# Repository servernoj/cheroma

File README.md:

# CheRoMa -- Chess Robotic Manipulator

This project represents work files to build and program a 4-DOF robotic manipulator intended to move chess pieces on the board by following live game broadcasted from chess.com (and lichess.org in near future) platforms. The arm is built from budgetary parts (servos, electromagnet, brackets) readily available for purchase from Amazon and other retailers. It also has a number of custom made 3D printed parts with CAD designs included in this repo.

As of April'26 this is a "work in progress" with completion rate of roughly 70-80%. The biggest challenge so far is the lack of precision of budgetary servos that negatively affects positioning of the arm in 3D space (error ±10mm) , which in turn results in inability for the arm to move specific chess piece from/to target position. This problem is being addressed by introducing a Digitizer -- platform allowing to calibrate robot's model params in real time by forcing it to move to specific positions and automatically reading 3D coordinates of the arrival point and using this data to fit model coefficients. 

## Demos

- Cheroma arm moving chess pieces https://www.youtube.com/shorts/CEkricqCiFo
- Cheroma Digitizer prototype is used for arm calibration https://www.youtube.com/shorts/9hFcoPiPavI

# Install the service

## Install NVM + Node + PNPM

Follow steps from https://github.com/nvm-sh/nvm?tab=readme-ov-file#installing-and-updating to install NVM

Then install `Node 22` and `pnpm`
```sh
nvm install 22
nvm alias default 22
npm i -g npm
```

## Install GitHub actions runner

Follow steps in `https://github.com/<username>/<repo>/settings/actions/runners/new`

## Install systemd service

Create file `/etc/systemd/system/cheroma.service` with the following content

```` ini
[Unit]
Description=CheRoMa API Service
After=network.target

[Service]
Type=simple
User=<username>
WorkingDirectory=/home/<username>/cheroma/apps/api
ExecStart=/bin/bash -lc 'source $HOME/.nvm/nvm.sh && node --env-file .env src/index.js'
Restart=on-failure
RestartSec=5
Environment=NODE_ENV=production
TimeoutStopSec=30s
KillSignal=SIGTERM
SendSIGKILL=yes

[Install]
WantedBy=multi-user.target
````
**Note**: replace `<username>` with your actual username on RasPi

Initialize the unit
```` sh
sudo systemctl daemon-reload
sudo systemctl start cheroma.service
````

Use the following to monitor the logs at realtime
```` sh
journalctl -u cheroma -f
```` 

# Misc
```sh
i2cset -y 1 0x40 0x00 0x10 # sleep
i2cset -y 1 0x40 0xFE 0x79 # frequency 50Hz
i2cset -y 1 0x40 0x00 0x20 # wake up + set auto-inc
i2cset -y 1 0x40 0x01 0x0C # set output + configure PWM reload logic

i2cset -y 1 0x40 0x06 0x00 0x00 0x40 0x01 i # center
```

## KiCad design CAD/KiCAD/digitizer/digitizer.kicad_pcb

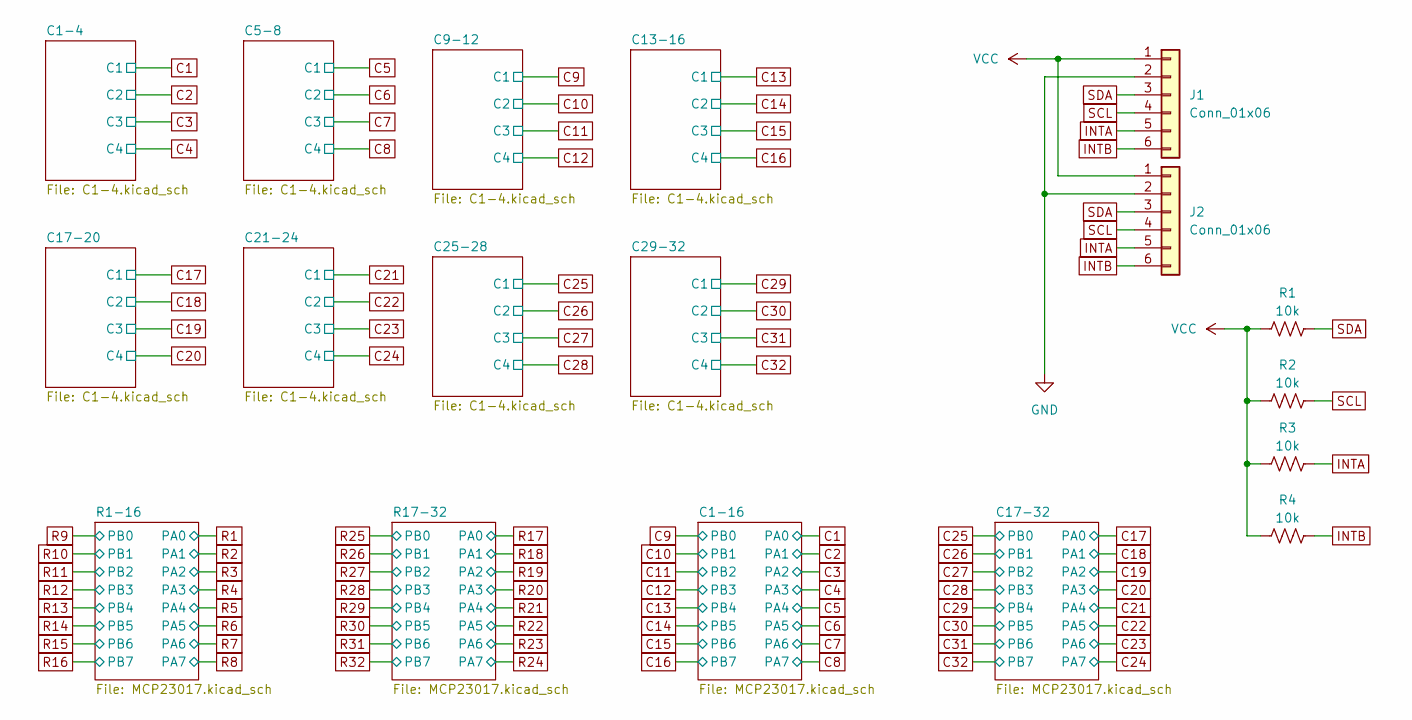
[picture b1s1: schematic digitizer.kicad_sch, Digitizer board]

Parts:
J1, J2: Conn_01x06; PinHeader_1x06_P2.54mm_Vertical
R1, R2, R3, R4: 10k; R_Axial_DIN0207_L6.3mm_D2.5mm_P15.24mm_Horizontal

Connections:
GND: J1.2, J2.2; also elsewhere on the board
INTA: J1.5, J2.5, R3.2; also elsewhere on the board
INTB: J1.6, J2.6, R4.2; also elsewhere on the board
SCL: J1.4, J2.4, R2.2; also elsewhere on the board
SDA: J1.3, J2.3, R1.2; also elsewhere on the board
VCC: J1.1, J2.1, R1.1, R2.1, R3.1, R4.1; also elsewhere on the board

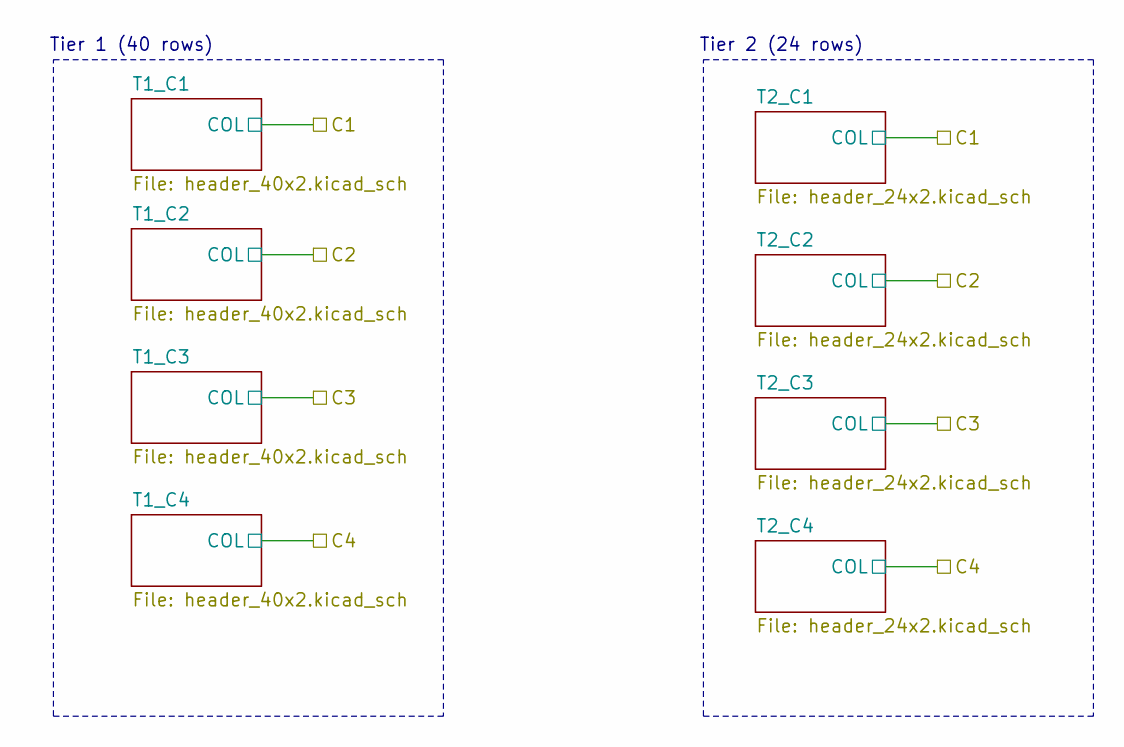
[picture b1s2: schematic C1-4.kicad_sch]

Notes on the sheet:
Tier 1 (40 rows)
Tier 2 (24 rows)

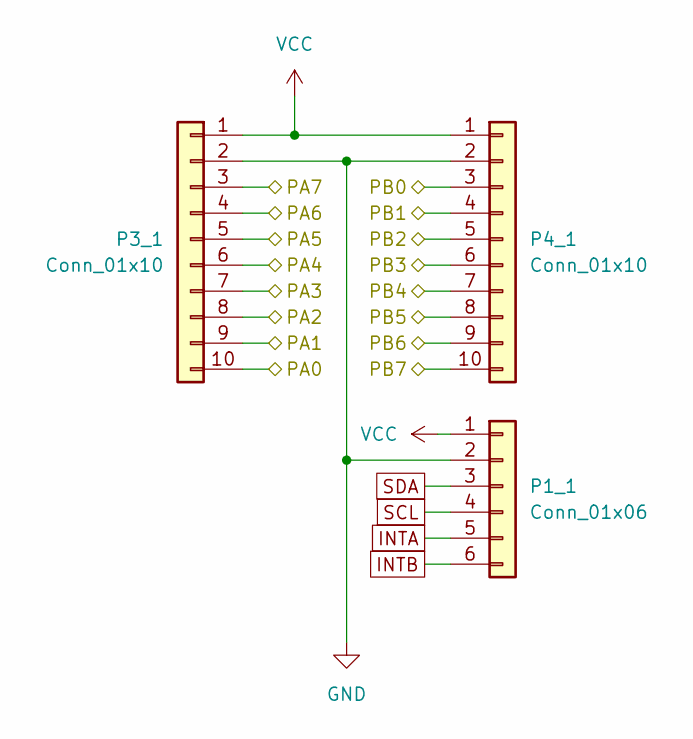
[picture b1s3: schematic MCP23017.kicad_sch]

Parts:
P1_1: Conn_01x06; PinSocket_1x06_P2.54mm_Vertical
P3_1, P4_1: Conn_01x10; PinSocket_1x10_P2.54mm_Vertical

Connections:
GND: P1_1.2, P3_1.2, P4_1.2; also elsewhere on the board
INTA: P1_1.5; also elsewhere on the board
INTB: P1_1.6; also elsewhere on the board
R1: P3_1.10; also elsewhere on the board
R2: P3_1.9; also elsewhere on the board
R3: P3_1.8; also elsewhere on the board
R4: P3_1.7; also elsewhere on the board
R5: P3_1.6; also elsewhere on the board
R6: P3_1.5; also elsewhere on the board
R7: P3_1.4; also elsewhere on the board
R8: P3_1.3; also elsewhere on the board
R9: P4_1.3; also elsewhere on the board
R10: P4_1.4; also elsewhere on the board
R11: P4_1.5; also elsewhere on the board
R12: P4_1.6; also elsewhere on the board
R13: P4_1.7; also elsewhere on the board
R14: P4_1.8; also elsewhere on the board
R15: P4_1.9; also elsewhere on the board
R16: P4_1.10; also elsewhere on the board
SCL: P1_1.4; also elsewhere on the board
SDA: P1_1.3; also elsewhere on the board
VCC: P1_1.1, P3_1.1, P4_1.1; also elsewhere on the board

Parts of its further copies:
P1_2, P1_3, P1_4: Conn_01x06; PinSocket_1x06_P2.54mm_Vertical
P3_2, P3_3, P3_4, P4_2, P4_3, P4_4: Conn_01x10; PinSocket_1x10_P2.54mm_Vertical

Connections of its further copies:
C1: P3_3.10; also elsewhere on the board
C2: P3_3.9; also elsewhere on the board
C3: P3_3.8; also elsewhere on the board
C4: P3_3.7; also elsewhere on the board
C5: P3_3.6; also elsewhere on the board
C6: P3_3.5; also elsewhere on the board
C7: P3_3.4; also elsewhere on the board
C8: P3_3.3; also elsewhere on the board
C9: P4_3.3; also elsewhere on the board
C10: P4_3.4; also elsewhere on the board
C11: P4_3.5; also elsewhere on the board
C12: P4_3.6; also elsewhere on the board
C13: P4_3.7; also elsewhere on the board
C14: P4_3.8; also elsewhere on the board
C15: P4_3.9; also elsewhere on the board
C16: P4_3.10; also elsewhere on the board
C17: P3_4.10; also elsewhere on the board
C18: P3_4.9; also elsewhere on the board
C19: P3_4.8; also elsewhere on the board
C20: P3_4.7; also elsewhere on the board
C21: P3_4.6; also elsewhere on the board
C22: P3_4.5; also elsewhere on the board
C23: P3_4.4; also elsewhere on the board
C24: P3_4.3; also elsewhere on the board
C25: P4_4.3; also elsewhere on the board
C26: P4_4.4; also elsewhere on the board
C27: P4_4.5; also elsewhere on the board
C28: P4_4.6; also elsewhere on the board
C29: P4_4.7; also elsewhere on the board
C30: P4_4.8; also elsewhere on the board
C31: P4_4.9; also elsewhere on the board
C32: P4_4.10; also elsewhere on the board
GND: P1_2.2, P1_3.2, P1_4.2, P3_2.2, P3_3.2, P3_4.2, P4_2.2, P4_3.2, P4_4.2; also elsewhere on the board
INTA: P1_2.5, P1_3.5, P1_4.5; also elsewhere on the board
INTB: P1_2.6, P1_3.6, P1_4.6; also elsewhere on the board
R17: P3_2.10; also elsewhere on the board
R18: P3_2.9; also elsewhere on the board
R19: P3_2.8; also elsewhere on the board
R20: P3_2.7; also elsewhere on the board
R21: P3_2.6; also elsewhere on the board
R22: P3_2.5; also elsewhere on the board
R23: P3_2.4; also elsewhere on the board
R24: P3_2.3; also elsewhere on the board
R25: P4_2.3; also elsewhere on the board
R26: P4_2.4; also elsewhere on the board
R27: P4_2.5; also elsewhere on the board
R28: P4_2.6; also elsewhere on the board
R29: P4_2.7; also elsewhere on the board
R30: P4_2.8; also elsewhere on the board
R31: P4_2.9; also elsewhere on the board
R32: P4_2.10; also elsewhere on the board
SCL: P1_2.4, P1_3.4, P1_4.4; also elsewhere on the board
SDA: P1_2.3, P1_3.3, P1_4.3; also elsewhere on the board
VCC: P1_2.1, P1_3.1, P1_4.1, P3_2.1, P3_3.1, P3_4.1, P4_2.1, P4_3.1, P4_4.1; also elsewhere on the board
